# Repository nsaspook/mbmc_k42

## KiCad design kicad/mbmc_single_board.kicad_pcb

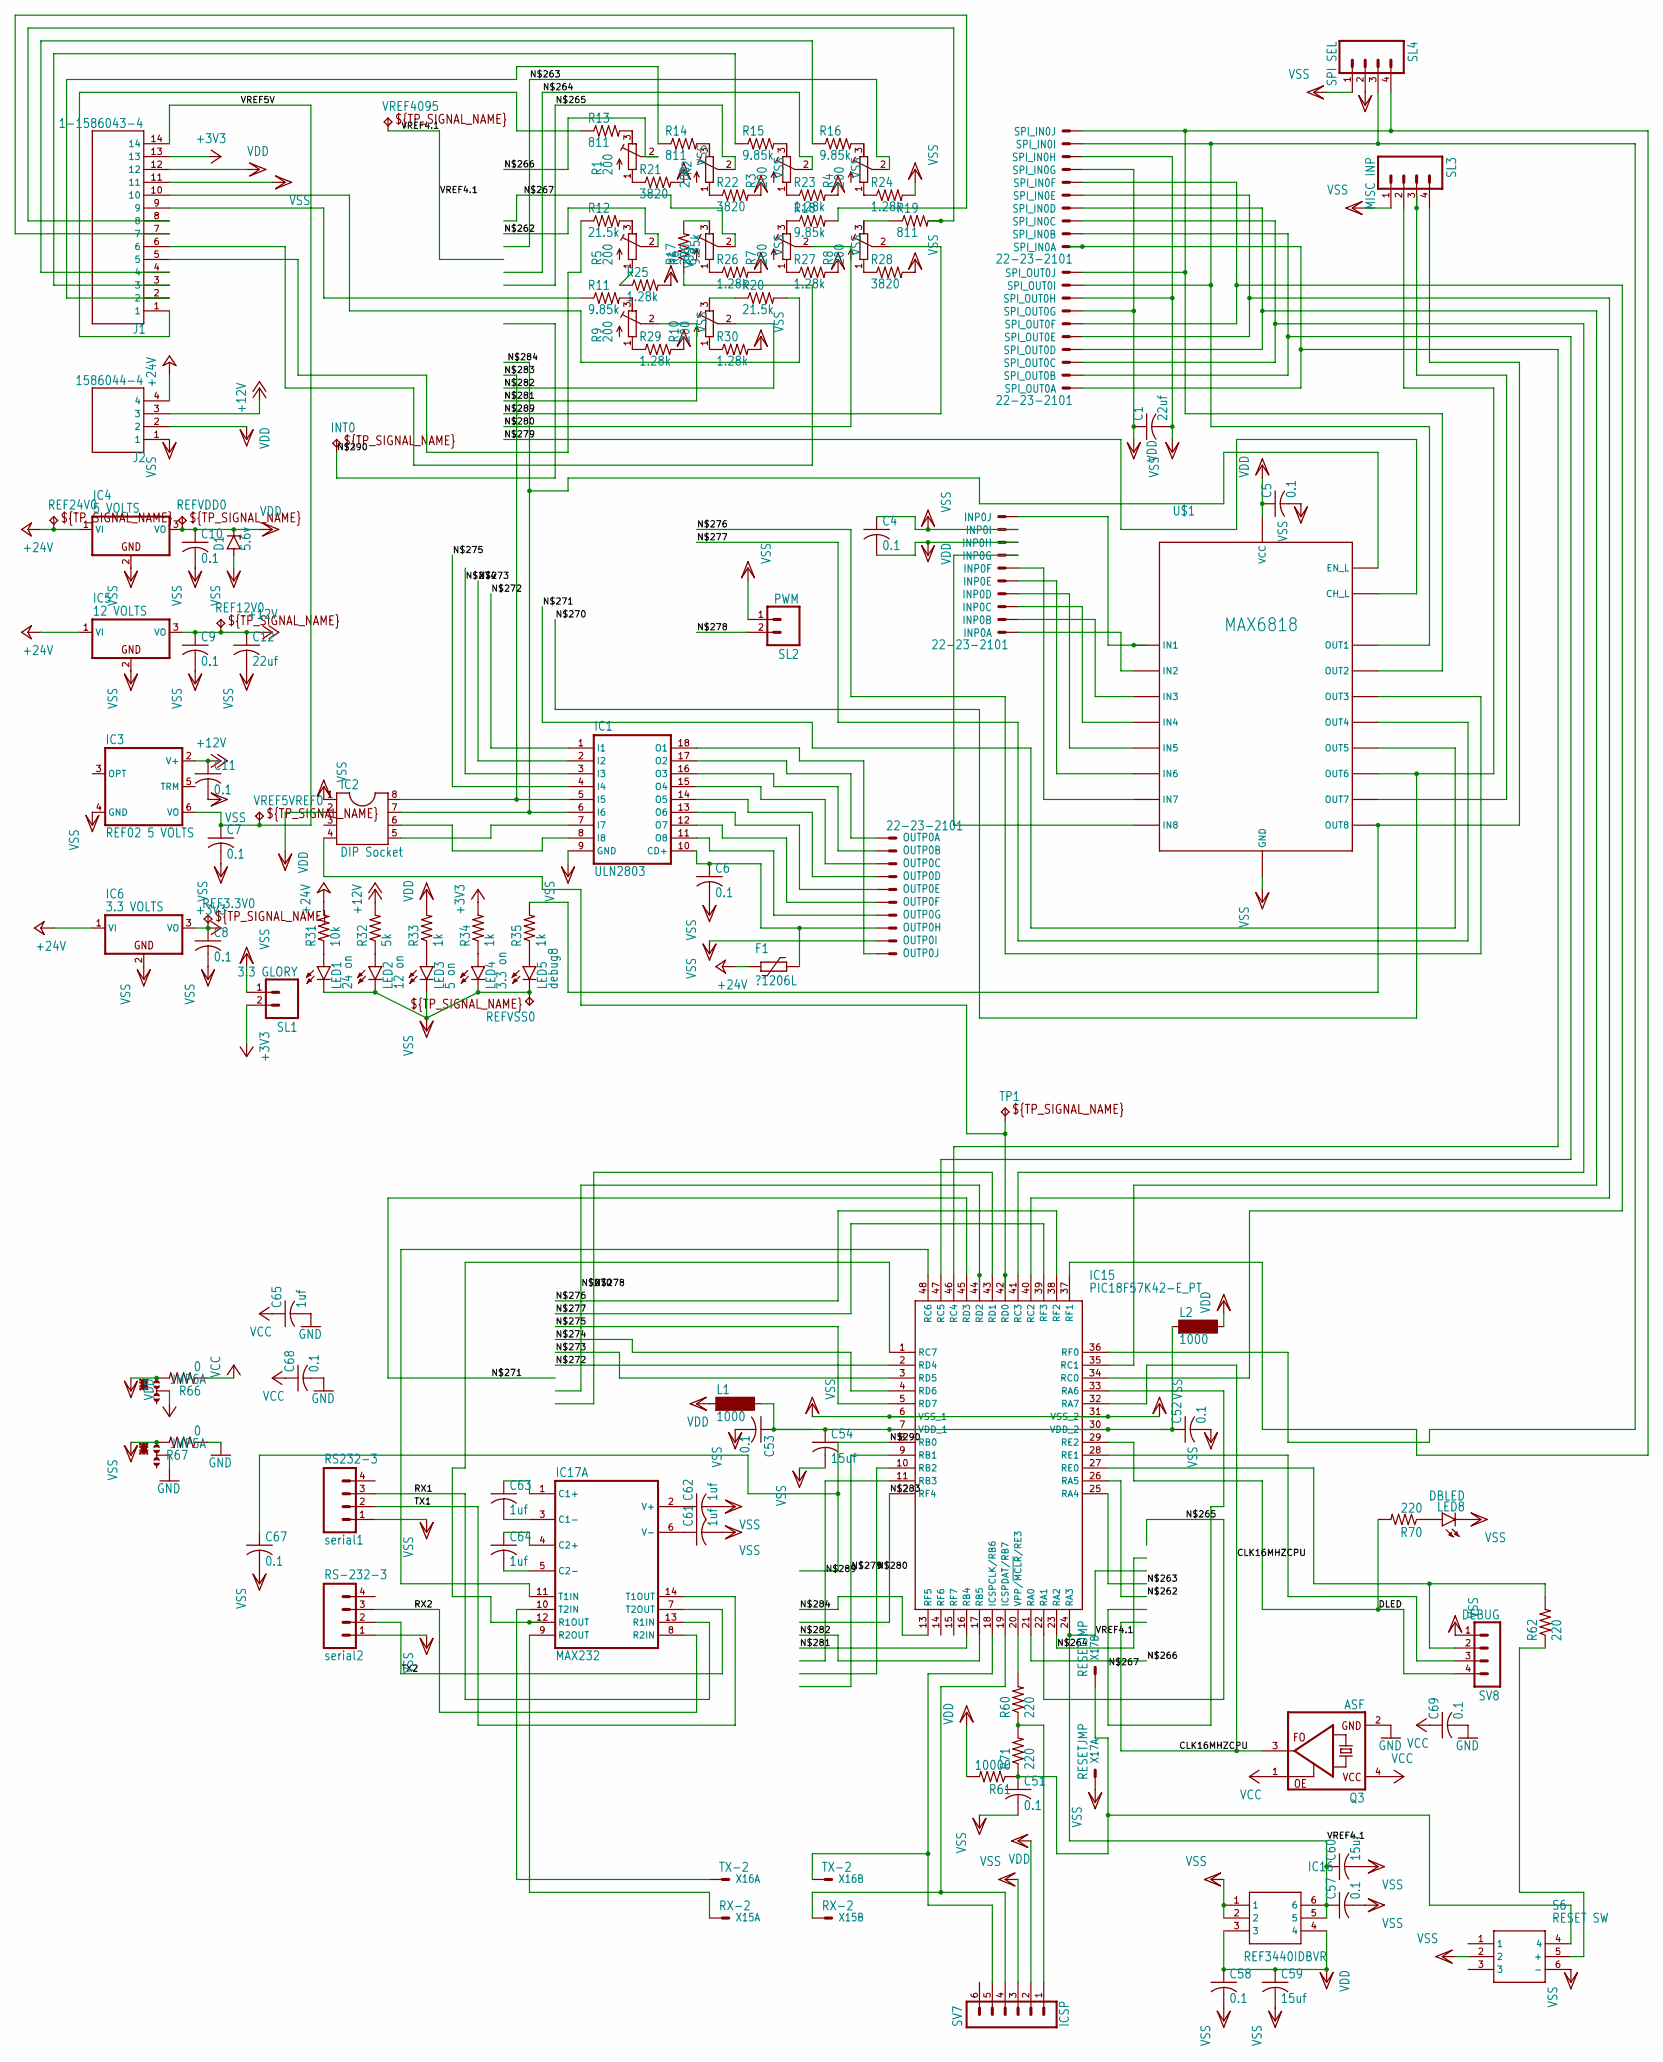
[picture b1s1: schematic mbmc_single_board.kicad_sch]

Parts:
C1, C12: 22uf; C0805
C4, C5, C6, C7, C8, C9, C10, C11: 0.1; C0805
C51, C52, C53, C57, C58, C67, C68, C69: 0.1; C1206
C54, C59, C60: 15uf; C1206
C61, C62, C63, C64, C65: 1uf; C0805
D1: 5.6v; ZDIO-2.5
F1: ?1206L; 1206L
IC1: ULN2803; DIL18
IC2: DIP Socket; SOCKET-08
IC3: REF02 5 VOLTS; DIL08
IC4: 5 VOLTS; TO220V
IC5: 12 VOLTS; TO220V
IC6: 3.3 VOLTS; TO220V
IC15: PIC18F57K42-E_PT; QFP50P900X900X120-48N
IC16: REF3440IDBVR; SOP95P280X145-6N
IC17: MAX232; DIL16
INP0: 22-23-2101
INT0: TPB1,27; B1,27
J1: 1-1586043-4; TE_1-1586043-4
J2: 1586044-4; TE_1586044-4
JMP5, JMP6: 0R-JUMPA; A0R-JMP
L1, L2: 1000; SM-1206
LED1: 24 on; CHIPLED_1206
LED2: 12 on; CHIPLED_1206
LED3: 5 on; CHIPLED_1206
LED4: 3.3 on; CHIPLED_1206
LED5: debug8; CHIPLED_1206
LED8: DBLED; CHIPLED_1206
OUTP0: 22-23-2101
Q3: ASF
R1, R2, R3, R4, R5, R6, R7, R8, R9, R10: 200; RTRIM3339P
R11, R15, R16, R17, R18: 9.85k; R0805
R12, R20: 21.5k; R0805
R13, R14, R19: 811; R0805
R21, R22, R28: 3820; R0805
R23, R24, R25, R26, R27, R29, R30: 1.28k; R0805
R31: 10k; R0805
R32: 5k; R0805
R33, R34, R35: 1k; R0805
R60, R62, R70, R71: 220; R1206
R61: 10000; R1206
R66, R67: 0; R1206
REF3.3V0, REF12V0, REF24V0: TPB1,27; B1,27
REFVDD0: TPB1,27; B1,27
REFVSS0: TPB1,27; B1,27
RS232-3: serial1; 04P
RS-232-3: serial2; 04P
S6: RESET SW; B3W-9_1-LED
SL1: 3.3 GLORY; 02P
SL2: PWM; 02P
SL3: MISC INP; 04P
SL4: SPI SEL; 04P
SPI_IN0: 22-23-2101
SPI_OUT0: 22-23-2101
SV7: ICSP; MA06-1
SV8: DEBUG; MA04-1
TP1: TPB1,27; B1,27
U$1: MAX6818; SSOP20
VREF5VREF0, VREF4095: TPB1,27; B1,27
X15: RX-2; 332-02
X16: TX-2; 332-02
X17: RESETJMP; 332-02

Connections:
+3V3: C8.1, IC6.3 (VO), J1.13, R34.2, REF3.3V0.TP, SL1.2
+12V: C9.1, C11.1, C12.1, IC3.2 (V+), IC5.3 (VO), J2.3, R32.2, REF12V0.TP
+24V: F1.2, IC4.1 (VI), IC5.1 (VI), IC6.1 (VI), J2.4, R31.2, REF24V0.TP
CLK16MHZCPU: IC15.32 (RA7), Q3.3 (FO)
DLED: IC15.29 (RE2), R70.2, SV8.4
GND: C65.2, C68.2, C69.2, IC17.15 (GND), JMP5.2, Q3.2 (GND), R67.1
unnamed: R9.3 (E), R11.2
unnamed: R5.3 (E), R12.2
unnamed: R1.3 (E), R13.2
unnamed: R2.3 (E), R14.2
unnamed: R3.3 (E), R15.2
unnamed: R4.3 (E), R16.2
unnamed: R6.3 (E), R17.2
unnamed: J1.7, R18.2
unnamed: R8.3 (E), R19.1
unnamed: J1.8, R19.2
unnamed: R1.1 (A), R21.1
unnamed: R2.1 (A), R22.1
unnamed: R3.1 (A), R23.1
unnamed: R4.1 (A), R24.1
unnamed: R5.1 (A), R25.1
unnamed: R6.1 (A), R26.1
unnamed: R7.1 (A), R27.1
unnamed: R8.1 (A), R28.1
unnamed: R9.1 (A), R29.1
unnamed: R10.1 (A), R30.1
unnamed: C6.1, F1.1, IC1.10 (CD+), OUTP0.8
unnamed: C52.1, C53.1, C54.1, IC15.7 (VDD_1), IC15.30 (VDD_2), L1.2, L2.1
unnamed: J1.2, R14.1
unnamed: IC1.7 (I7), IC2.5
unnamed: IC1.8 (I8), IC2.6
unnamed: IC15.36 (RF0), SL4.3, SPI_IN0.9, SPI_OUT0.9, U$1.OUT1
unnamed: INP0.10, U$1.IN1
unnamed: INP0.1, U$1.IN2
unnamed: INP0.2, U$1.IN3
unnamed: INP0.3, U$1.IN4
unnamed: INP0.4, U$1.IN5
unnamed: INP0.5, U$1.IN6
unnamed: INP0.6, U$1.IN7
unnamed: INP0.7, U$1.IN8
unnamed: IC1.18 (O1), OUTP0.10
unnamed: IC1.17 (O2), OUTP0.1
unnamed: IC1.16 (O3), OUTP0.2
unnamed: IC1.15 (O4), OUTP0.3
unnamed: IC1.14 (O5), OUTP0.4
unnamed: IC1.13 (O6), OUTP0.5
unnamed: IC1.12 (O7), OUTP0.6
unnamed: IC1.11 (O8), OUTP0.7
unnamed: IC15.46 (RC4), SPI_IN0.1, SPI_OUT0.1
unnamed: J1.4, R16.1
unnamed: J1.9, R11.1
unnamed: J1.3, R15.1
unnamed: J1.10, R20.2
unnamed: J1.5, R12.1
unnamed: J1.6, R17.1
unnamed: J1.1, R13.1
unnamed: LED1.A, R31.1
unnamed: LED2.A, R32.1
unnamed: LED3.A, R33.1
unnamed: LED4.A, R34.1
unnamed: LED5.A, R35.1
unnamed: R35.2, SL3.4, U$1.OUT8
unnamed: R10.3 (E), R20.1
unnamed: SL3.3, U$1.OUT7
unnamed: R7.3 (E), R18.1
unnamed: IC15.20 (VPP/~MCLR/RE3), R60.2
unnamed: IC15.19 (ICSPDAT/RB7), SV7.4, X15.2
unnamed: IC15.18 (ICSPCLK/RB6), SV7.5, X16.2
unnamed: C61.1, IC17.6 (V-)
unnamed: C62.1, IC17.2 (V+)
unnamed: C63.1, IC17.1 (C1+)
unnamed: C64.1, IC17.4 (C2+)
unnamed: C64.2, IC17.5 (C2-)
unnamed: C63.2, IC17.3 (C1-)
unnamed: IC15.1 (RC7), IC17.12 (R1OUT)
unnamed: IC17.9 (R2OUT), X15.1
unnamed: IC15.48 (RC6), IC17.11 (T1IN)
unnamed: IC17.10 (T2IN), X16.1
unnamed: R62.1, S6.5 (+)
unnamed: IC15.27 (RE0), R62.2, SV8.2
unnamed: IC15.28 (RE1), SV8.3
unnamed: IC2.4, IC15.42 (RD0), TP1.TP
unnamed: IC15.47 (RC5), SPI_IN0.2, SPI_OUT0.2
unnamed: IC15.41 (RC3), SPI_IN0.3, SPI_OUT0.3
unnamed: IC15.35 (RC1), SPI_IN0.4, SPI_OUT0.4
unnamed: IC15.40 (RC2), SPI_IN0.5, SPI_OUT0.5
unnamed: IC15.34 (RC0), SPI_IN0.6, SPI_OUT0.6
unnamed: IC15.26 (RA5), R5.2 (S)
unnamed: IC15.25 (RA4), R4.2 (S)
unnamed: IC15.23 (RA2), R3.2 (S)
unnamed: IC15.22 (RA1), R2.2 (S)
unnamed: IC15.21 (RA0), R1.2 (S)
unnamed: IC15.33 (RA6), R6.2 (S)
unnamed: IC15.37 (RF1), SL4.4, SPI_IN0.10, SPI_OUT0.10, U$1.OUT2
unnamed: IC15.44 (RD2), SL3.2, U$1.OUT6
unnamed: IC15.45 (RD3), U$1.OUT5
unnamed: IC1.1 (I1), IC15.2 (RD4)
unnamed: IC1.2 (I2), IC15.3 (RD5)
unnamed: IC1.3 (I3), IC15.4 (RD6)
unnamed: IC1.4 (I4), IC15.5 (RD7)
unnamed: IC15.38 (RF2), U$1.OUT3
unnamed: IC15.39 (RF3), U$1.OUT4
unnamed: IC15.43 (RD1), SL2.2
unnamed: IC15.9 (RB1), U$1.CH_L
unnamed: IC15.10 (RB2), R7.2 (S)
unnamed: IC15.16 (RB4), R9.2 (S)
unnamed: IC15.17 (RB5), R10.2 (S)
unnamed: IC1.5 (I5), IC2.8, IC15.12 (RF4)
unnamed: IC1.6 (I6), IC2.7, IC15.13 (RF5), U$1.EN_L
unnamed: IC15.11 (RB3), R8.2 (S)
unnamed: C67.1, IC15.8 (RB0), INT0.TP
unnamed: LED8.A, R70.1
unnamed: C51.1, R61.1, R71.1, S6.4, X17.2
unnamed: R60.1, R71.2, SV7.1
RX1: IC17.13 (R1IN), RS232-3.3
RX2: IC17.8 (R2IN), RS-232-3.3
TX1: IC17.14 (T1OUT), RS232-3.2
TX2: IC17.7 (T2OUT), RS-232-3.2
VCC: C65.1, C68.1, C69.1, IC17.16 (VCC), JMP6.2, Q3.1 (OE), Q3.4 (VCC), R66.1
VDD: C1.1, C4.2, C5.1, C10.1, C58.1, C59.1, D1.C, IC2.2, IC4.3 (VO), IC16.3, IC16.4, INP0.8, J1.12, J2.2, JMP6.1, L1.1, L2.2, R33.2, R61.2, R66.2, REFVDD0.TP, SL4.2, SPI_IN0.7, SPI_OUT0.7, SV7.2, U$1.VCC
VREF4.1: C57.1, C60.1, IC15.24 (RA3), IC16.5, IC16.6, VREF4095.TP
VREF5V: C7.1, IC3.6 (VO), J1.14, VREF5VREF0.TP
VSS: C1.2, C4.1, C5.2, C6.2, C7.2, C8.2, C9.2, C10.2, C11.2, C12.2, C51.2, C52.2, C53.2, C54.2, C57.2, C58.2, C59.2, C60.2, C61.2, C62.2, C67.2, D1.A, IC1.9 (GND), IC2.1, IC3.4 (GND), IC4.2 (GND), IC5.2 (GND), IC6.2 (GND), IC15.6 (VSS_1), IC15.31 (VSS_2), IC16.1, IC16.2, INP0.9, J1.11, J2.1, JMP5.1, LED1.C, LED2.C, LED3.C, LED4.C, LED5.C, LED8.C, OUTP0.9, R21.2, R22.2, R23.2, R24.2, R25.2, R26.2, R27.2, R28.2, R29.2, R30.2, R67.2, REFVSS0.TP, RS232-3.1, RS-232-3.1, S6.2, S6.6 (-), SL1.1, SL2.1, SL3.1, SL4.1, SPI_IN0.8, SPI_OUT0.8, SV7.3, SV8.1, U$1.GND, X17.1

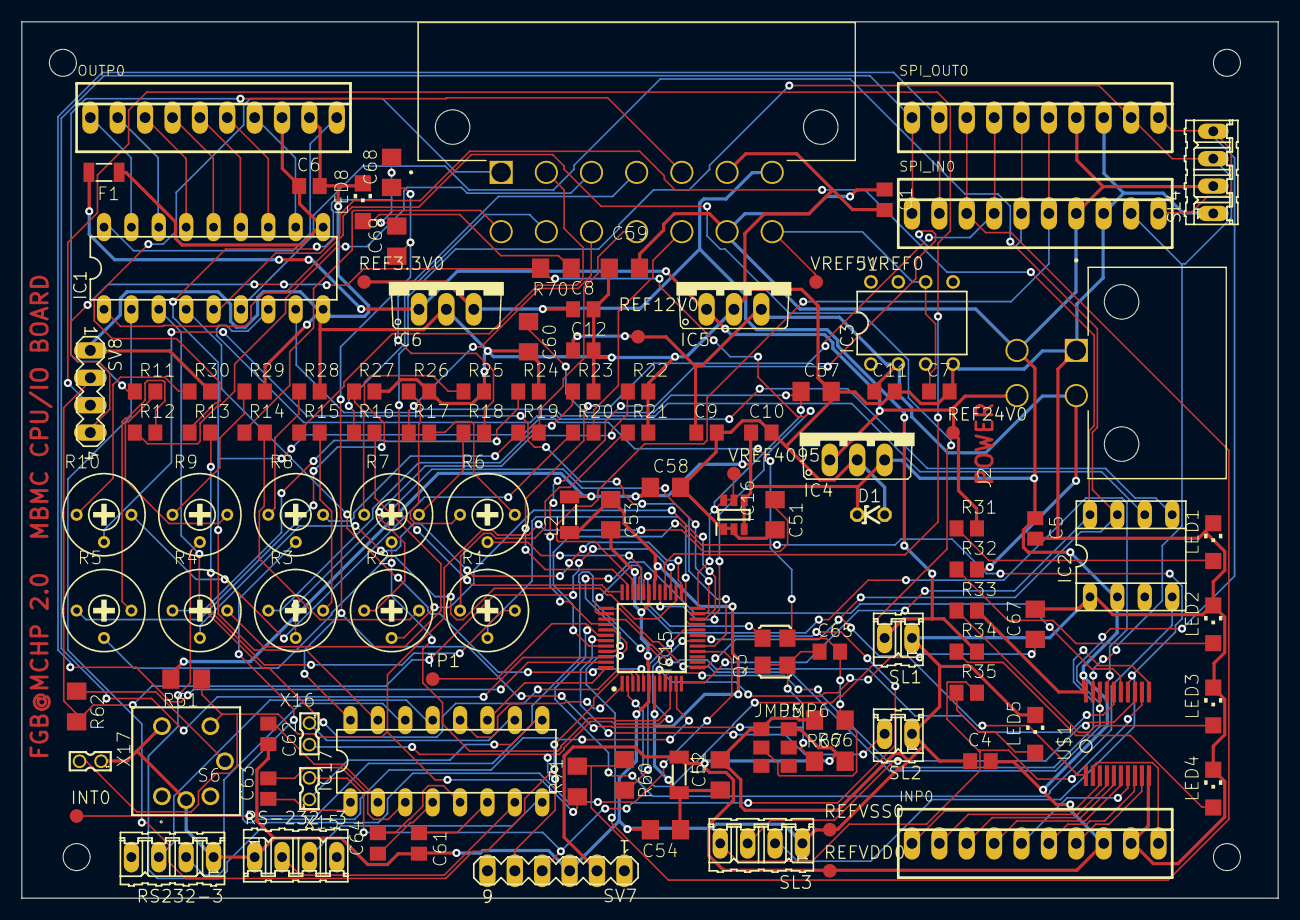
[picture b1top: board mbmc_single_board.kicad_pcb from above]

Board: 2 copper layers, 116.5 x 81.3 mm, 122 parts (0 on the bottom side), 123 nets.

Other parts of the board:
@HOLE0, @HOLE1, @HOLE2, @HOLE3: (no value)

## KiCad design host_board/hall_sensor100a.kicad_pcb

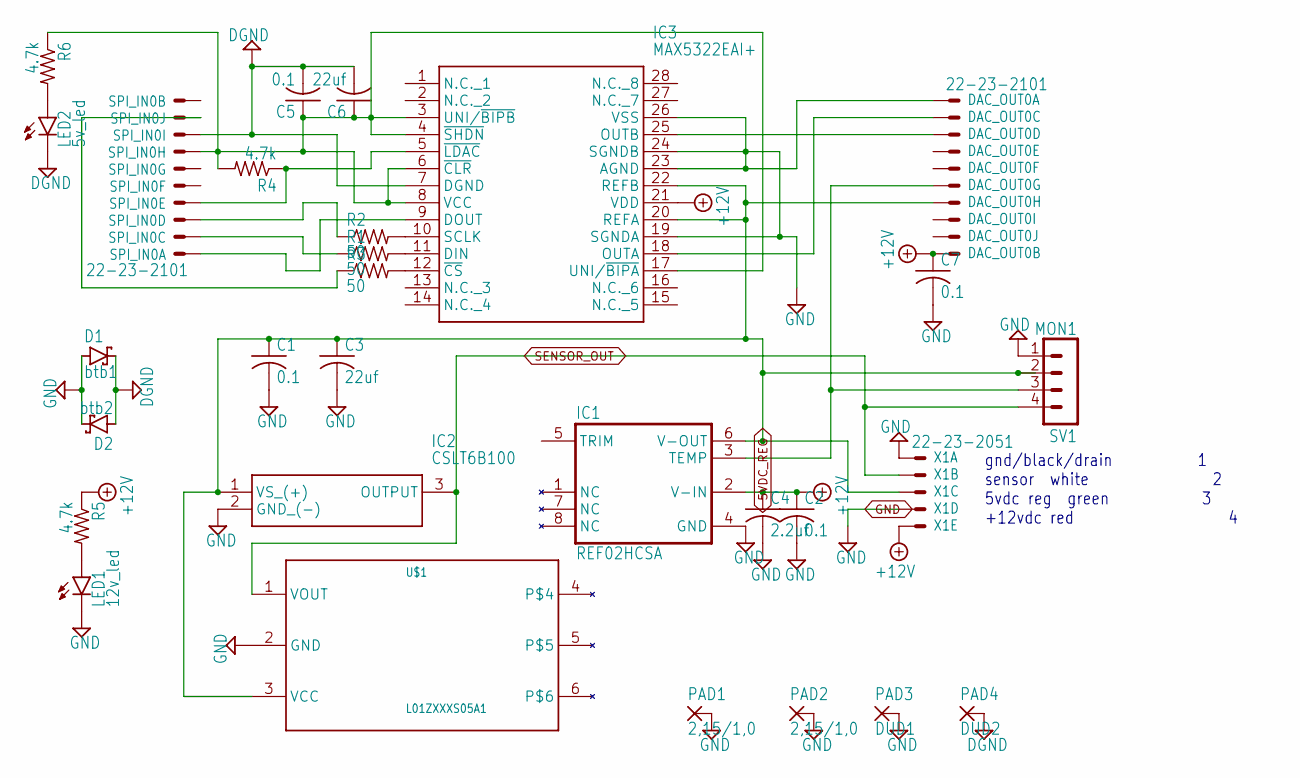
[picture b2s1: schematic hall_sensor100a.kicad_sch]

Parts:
C1, C2, C5, C7: 0.1; C0805
C3, C6: 22uf; C0805
C4: 2.2uf; C0805
D1: btb1; DO35-7
D2: btb2; DO35-7
DAC_OUT0: 22-23-2101; MPN 22-23-2101
IC1: REF02HCSA; SO08
IC2: CSLT6B100; MANUFACTURER_PART_NUMBER CSLT6B100; MOUSER_PART_NUMBER 785-CSLT6B100
IC3: MAX5322EAI+; SOP65P778X199-28N; MANUFACTURER_PART_NUMBER MAX5322EAI+; MOUSER_PART_NUMBER 700-MAX5322EAI
LED1: 12v_led; CHIPLED_1206
LED2: 5v_led; CHIPLED_1206
PAD1, PAD2: 2,15/1,0; 2,15_1,0
PAD3: DUD1; 2,15_1,0
PAD4: DUD2; 2,15_1,0
R1, R2, R3: 50; M0805
R4, R5, R6: 4.7k; M0805
SPI_IN0: 22-23-2101; MPN 22-23-2101
SV1: MON1; MA04-1
U$1: L01ZXXXS05A1; DIP2540W53P254L2900H508Q6B
X1: 22-23-2051; MPN 22-23-2051

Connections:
5VDC_REG: C1.1, C3.1, DAC_OUT0.7, IC1.6 (V-OUT), IC2.1 (VS_(+)), IC3.20 (REFA), IC3.22 (REFB), SV1.2, U$1.3 (VCC), X1.3
+12V: C2.1, C4.1, C7.1, DAC_OUT0.10, IC1.2 (V-IN), IC3.21 (VDD), R5.1, X1.5
DGND: C5.2, C6.2, D1.C, D2.A, IC3.7 (DGND), LED2.C, PAD4.1, SPI_IN0.8
GND: C1.2, C2.2, C3.2, C4.2, C7.2, D1.A, D2.C, DAC_OUT0.1, IC1.4 (GND), IC2.2 (GND_(-)), IC3.19 (SGNDA), IC3.23 (AGND), IC3.24 (SGNDB), IC3.26 (VSS), LED1.C, PAD1.1, PAD2.1, PAD3.1, SV1.1, U$1.2 (GND), X1.1, X1.4
unnamed: IC3.11 (DIN), R1.2
unnamed: DAC_OUT0.2, IC3.18 (OUTA)
unnamed: DAC_OUT0.3, IC3.25 (OUTB)
unnamed: R1.1, SPI_IN0.2
unnamed: IC3.9 (DOUT), SPI_IN0.1
unnamed: R2.1, SPI_IN0.3
unnamed: R3.1, SPI_IN0.9
unnamed: C5.1, C6.1, IC3.3 (UNI/~BIPB), IC3.4 (~SHDN), IC3.6 (~CLR), IC3.8 (VCC), IC3.17 (UNI/~BIPA), R4.2, R6.1, SPI_IN0.7
unnamed: LED1.A, R5.2
unnamed: IC3.5 (~LDAC), R4.1, SPI_IN0.4
unnamed: IC3.10 (SCLK), R2.2
unnamed: IC3.12 (~CS), R3.2
unnamed: DAC_OUT0.6, IC1.3 (TEMP), SV1.3
unnamed: LED2.A, R6.2
SENSOR_OUT: IC2.3 (OUTPUT), SV1.4, U$1.1 (VOUT), X1.2

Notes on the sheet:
gnd/black/drain 1 sensor white 2 5vdc reg green 3 +12vdc red 4

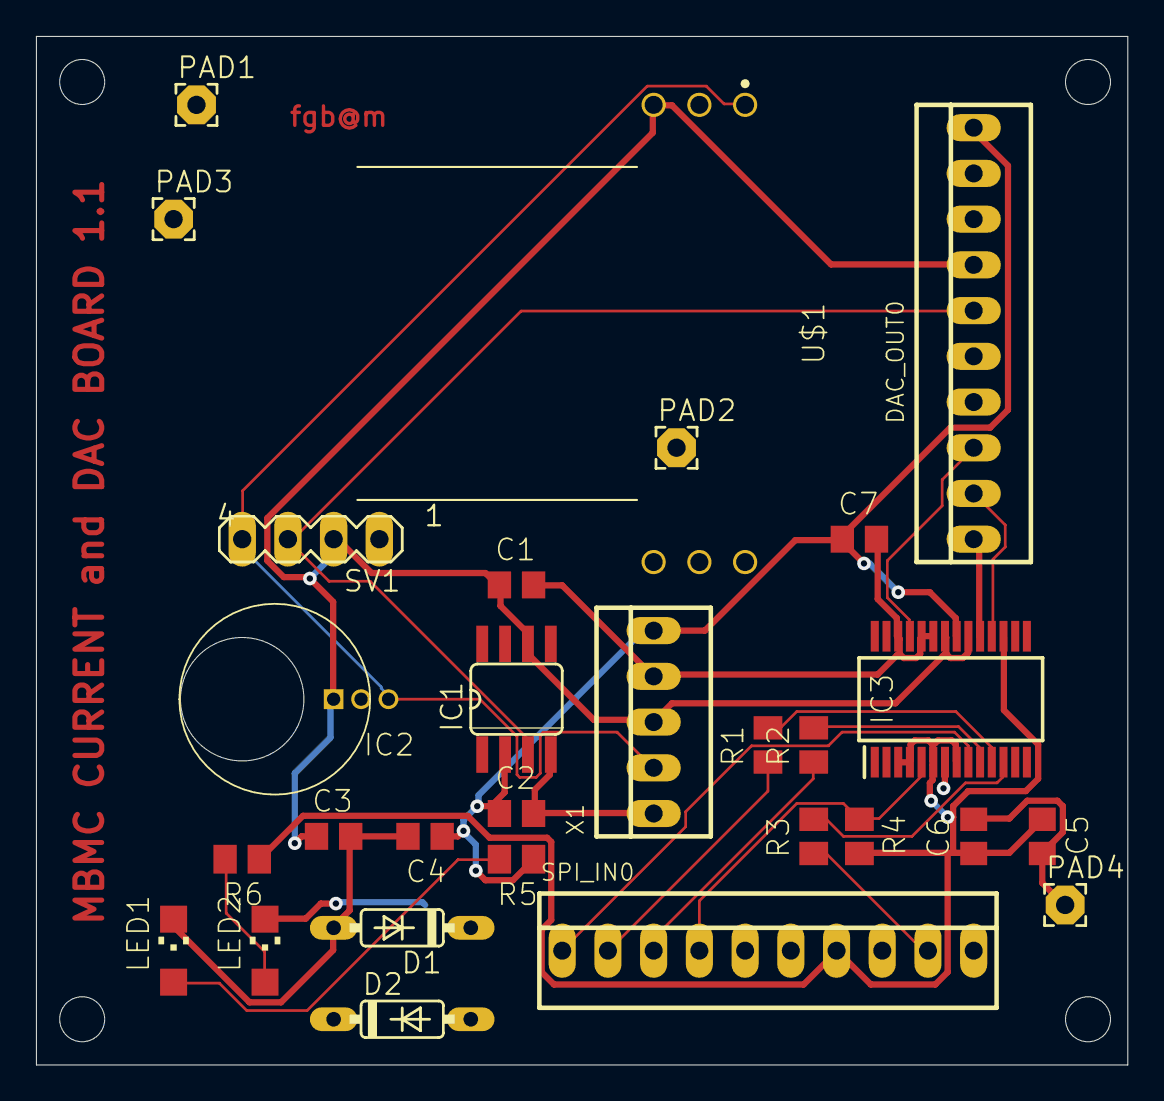
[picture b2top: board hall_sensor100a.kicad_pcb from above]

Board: 2 copper layers, 60.6 x 57.1 mm, 34 parts (0 on the bottom side), 19 nets.

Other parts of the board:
UNK_HOLE_0: dummyfp0
UNK_HOLE_1: dummyfp1
UNK_HOLE_2: dummyfp2
UNK_HOLE_3: dummyfp3
UNK_HOLE_4: dummyfp4

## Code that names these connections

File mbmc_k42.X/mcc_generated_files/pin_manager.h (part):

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// get/set C_BATT aliases
#define C_BATT_TRIS                 TRISAbits.TRISA0
#define C_BATT_LAT                  LATAbits.LATA0
#define C_BATT_PORT                 PORTAbits.RA0
#define C_BATT_WPU                  WPUAbits.WPUA0
#define C_BATT_OD                   ODCONAbits.ODCA0
#define C_BATT_ANS                  ANSELAbits.ANSELA0
#define C_BATT_SetHigh()            do { LATAbits.LATA0 = 1; } while(0)
#define C_BATT_SetLow()             do { LATAbits.LATA0 = 0; } while(0)
#define C_BATT_Toggle()             do { LATAbits.LATA0 = ~LATAbits.LATA0; } while(0)
#define C_BATT_GetValue()           PORTAbits.RA0
#define C_BATT_SetDigitalInput()    do { TRISAbits.TRISA0 = 1; } while(0)
#define C_BATT_SetDigitalOutput()   do { TRISAbits.TRISA0 = 0; } while(0)
#define C_BATT_SetPullup()          do { WPUAbits.WPUA0 = 1; } while(0)
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// get/set C_PV aliases
#define C_PV_TRIS                 TRISAbits.TRISA1
#define C_PV_LAT                  LATAbits.LATA1
#define C_PV_PORT                 PORTAbits.RA1
#define C_PV_WPU                  WPUAbits.WPUA1
#define C_PV_OD                   ODCONAbits.ODCA1
#define C_PV_ANS                  ANSELAbits.ANSELA1
#define C_PV_SetHigh()            do { LATAbits.LATA1 = 1; } while(0)
#define C_PV_SetLow()             do { LATAbits.LATA1 = 0; } while(0)
#define C_PV_Toggle()             do { LATAbits.LATA1 = ~LATAbits.LATA1; } while(0)
#define C_PV_GetValue()           PORTAbits.RA1
#define C_PV_SetDigitalInput()    do { TRISAbits.TRISA1 = 1; } while(0)
#define C_PV_SetDigitalOutput()   do { TRISAbits.TRISA1 = 0; } while(0)
#define C_PV_SetPullup()          do { WPUAbits.WPUA1 = 1; } while(0)
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// get/set V_CC aliases
#define V_CC_TRIS                 TRISAbits.TRISA2
#define V_CC_LAT                  LATAbits.LATA2
#define V_CC_PORT                 PORTAbits.RA2
#define V_CC_WPU                  WPUAbits.WPUA2
#define V_CC_OD                   ODCONAbits.ODCA2
#define V_CC_ANS                  ANSELAbits.ANSELA2
#define V_CC_SetHigh()            do { LATAbits.LATA2 = 1; } while(0)
#define V_CC_SetLow()             do { LATAbits.LATA2 = 0; } while(0)
#define V_CC_Toggle()             do { LATAbits.LATA2 = ~LATAbits.LATA2; } while(0)
#define V_CC_GetValue()           PORTAbits.RA2
#define V_CC_SetDigitalInput()    do { TRISAbits.TRISA2 = 1; } while(0)
#define V_CC_SetDigitalOutput()   do { TRISAbits.TRISA2 = 0; } while(0)
#define V_CC_SetPullup()          do { WPUAbits.WPUA2 = 1; } while(0)
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#define RA3_SetHigh()            do { LATAbits.LATA3 = 1; } while(0)
#define RA3_SetLow()             do { LATAbits.LATA3 = 0; } while(0)
#define RA3_Toggle()             do { LATAbits.LATA3 = ~LATAbits.LATA3; } while(0)
#define RA3_GetValue()              PORTAbits.RA3
#define RA3_SetDigitalInput()    do { TRISAbits.TRISA3 = 1; } while(0)
#define RA3_SetDigitalOutput()   do { TRISAbits.TRISA3 = 0; } while(0)
#define RA3_SetPullup()             do { WPUAbits.WPUA3 = 1; } while(0)
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// get/set V_BAT aliases
#define V_BAT_TRIS                 TRISAbits.TRISA4
#define V_BAT_LAT                  LATAbits.LATA4
#define V_BAT_PORT                 PORTAbits.RA4
#define V_BAT_WPU                  WPUAbits.WPUA4
#define V_BAT_OD                   ODCONAbits.ODCA4
#define V_BAT_ANS                  ANSELAbits.ANSELA4
#define V_BAT_SetHigh()            do { LATAbits.LATA4 = 1; } while(0)
#define V_BAT_SetLow()             do { LATAbits.LATA4 = 0; } while(0)
#define V_BAT_Toggle()             do { LATAbits.LATA4 = ~LATAbits.LATA4; } while(0)
#define V_BAT_GetValue()           PORTAbits.RA4
#define V_BAT_SetDigitalInput()    do { TRISAbits.TRISA4 = 1; } while(0)
#define V_BAT_SetDigitalOutput()   do { TRISAbits.TRISA4 = 0; } while(0)
#define V_BAT_SetPullup()          do { WPUAbits.WPUA4 = 1; } while(0)
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// get/set V_PV aliases
#define V_PV_TRIS                 TRISAbits.TRISA5
#define V_PV_LAT                  LATAbits.LATA5
#define V_PV_PORT                 PORTAbits.RA5
#define V_PV_WPU                  WPUAbits.WPUA5
#define V_PV_OD                   ODCONAbits.ODCA5
#define V_PV_ANS                  ANSELAbits.ANSELA5
#define V_PV_SetHigh()            do { LATAbits.LATA5 = 1; } while(0)
#define V_PV_SetLow()             do { LATAbits.LATA5 = 0; } while(0)
#define V_PV_Toggle()             do { LATAbits.LATA5 = ~LATAbits.LATA5; } while(0)
#define V_PV_GetValue()           PORTAbits.RA5
#define V_PV_SetDigitalInput()    do { TRISAbits.TRISA5 = 1; } while(0)
#define V_PV_SetDigitalOutput()   do { TRISAbits.TRISA5 = 0; } while(0)
#define V_PV_SetPullup()          do { WPUAbits.WPUA5 = 1; } while(0)
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// get/set V_CMODE aliases
#define V_CMODE_TRIS                 TRISAbits.TRISA6
#define V_CMODE_LAT                  LATAbits.LATA6
#define V_CMODE_PORT                 PORTAbits.RA6
#define V_CMODE_WPU                  WPUAbits.WPUA6
#define V_CMODE_OD                   ODCONAbits.ODCA6
#define V_CMODE_ANS                  ANSELAbits.ANSELA6
#define V_CMODE_SetHigh()            do { LATAbits.LATA6 = 1; } while(0)
#define V_CMODE_SetLow()             do { LATAbits.LATA6 = 0; } while(0)
#define V_CMODE_Toggle()             do { LATAbits.LATA6 = ~LATAbits.LATA6; } while(0)
#define V_CMODE_GetValue()           PORTAbits.RA6
#define V_CMODE_SetDigitalInput()    do { TRISAbits.TRISA6 = 1; } while(0)
#define V_CMODE_SetDigitalOutput()   do { TRISAbits.TRISA6 = 0; } while(0)
#define V_CMODE_SetPullup()          do { WPUAbits.WPUA6 = 1; } while(0)
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#define RB0_SetHigh()            do { LATBbits.LATB0 = 1; } while(0)
#define RB0_SetLow()             do { LATBbits.LATB0 = 0; } while(0)
#define RB0_Toggle()             do { LATBbits.LATB0 = ~LATBbits.LATB0; } while(0)
#define RB0_GetValue()              PORTBbits.RB0
#define RB0_SetDigitalInput()    do { TRISBbits.TRISB0 = 1; } while(0)
#define RB0_SetDigitalOutput()   do { TRISBbits.TRISB0 = 0; } while(0)
#define RB0_SetPullup()             do { WPUBbits.WPUB0 = 1; } while(0)
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#define RB1_SetHigh()            do { LATBbits.LATB1 = 1; } while(0)
#define RB1_SetLow()             do { LATBbits.LATB1 = 0; } while(0)
#define RB1_Toggle()             do { LATBbits.LATB1 = ~LATBbits.LATB1; } while(0)
#define RB1_GetValue()              PORTBbits.RB1
#define RB1_SetDigitalInput()    do { TRISBbits.TRISB1 = 1; } while(0)
#define RB1_SetDigitalOutput()   do { TRISBbits.TRISB1 = 0; } while(0)
#define RB1_SetPullup()             do { WPUBbits.WPUB1 = 1; } while(0)
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// get/set V_BBAT aliases
#define V_BBAT_TRIS                 TRISBbits.TRISB2
#define V_BBAT_LAT                  LATBbits.LATB2
#define V_BBAT_PORT                 PORTBbits.RB2
#define V_BBAT_WPU                  WPUBbits.WPUB2
#define V_BBAT_OD                   ODCONBbits.ODCB2
#define V_BBAT_ANS                  ANSELBbits.ANSELB2
#define V_BBAT_SetHigh()            do { LATBbits.LATB2 = 1; } while(0)
#define V_BBAT_SetLow()             do { LATBbits.LATB2 = 0; } while(0)
#define V_BBAT_Toggle()             do { LATBbits.LATB2 = ~LATBbits.LATB2; } while(0)
#define V_BBAT_GetValue()           PORTBbits.RB2
#define V_BBAT_SetDigitalInput()    do { TRISBbits.TRISB2 = 1; } while(0)
#define V_BBAT_SetDigitalOutput()   do { TRISBbits.TRISB2 = 0; } while(0)
#define V_BBAT_SetPullup()          do { WPUBbits.WPUB2 = 1; } while(0)
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// get/set C_MPPT aliases
#define C_MPPT_TRIS                 TRISBbits.TRISB3
#define C_MPPT_LAT                  LATBbits.LATB3
#define C_MPPT_PORT                 PORTBbits.RB3
#define C_MPPT_WPU                  WPUBbits.WPUB3
#define C_MPPT_OD                   ODCONBbits.ODCB3
#define C_MPPT_ANS                  ANSELBbits.ANSELB3
#define C_MPPT_SetHigh()            do { LATBbits.LATB3 = 1; } while(0)
#define C_MPPT_SetLow()             do { LATBbits.LATB3 = 0; } while(0)
#define C_MPPT_Toggle()             do { LATBbits.LATB3 = ~LATBbits.LATB3; } while(0)
#define C_MPPT_GetValue()           PORTBbits.RB3
#define C_MPPT_SetDigitalInput()    do { TRISBbits.TRISB3 = 1; } while(0)
#define C_MPPT_SetDigitalOutput()   do { TRISBbits.TRISB3 = 0; } while(0)
#define C_MPPT_SetPullup()          do { WPUBbits.WPUB3 = 1; } while(0)
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// get/set V_INVERTER aliases
#define V_INVERTER_TRIS                 TRISBbits.TRISB4
#define V_INVERTER_LAT                  LATBbits.LATB4
#define V_INVERTER_PORT                 PORTBbits.RB4
#define V_INVERTER_WPU                  WPUBbits.WPUB4
#define V_INVERTER_OD                   ODCONBbits.ODCB4
#define V_INVERTER_ANS                  ANSELBbits.ANSELB4
#define V_INVERTER_SetHigh()            do { LATBbits.LATB4 = 1; } while(0)
#define V_INVERTER_SetLow()             do { LATBbits.LATB4 = 0; } while(0)
#define V_INVERTER_Toggle()             do { LATBbits.LATB4 = ~LATBbits.LATB4; } while(0)
#define V_INVERTER_GetValue()           PORTBbits.RB4
#define V_INVERTER_SetDigitalInput()    do { TRISBbits.TRISB4 = 1; } while(0)
#define V_INVERTER_SetDigitalOutput()   do { TRISBbits.TRISB4 = 0; } while(0)
#define V_INVERTER_SetPullup()          do { WPUBbits.WPUB4 = 1; } while(0)
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// get/set V_LIGHT_SENSOR aliases
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
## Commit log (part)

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2020-11-29 new git for MBMC for 24 volt systems
2024-01-30 alpha version 2.10
2024-10-19 correct AH calcs
2025-03-19 clean up files for doxygen docs
2025-08-19 checkpoint

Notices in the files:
mbmc_k42.X/mcc_generated_files/pin_manager.h:
(c) 2018 Microchip Technology Inc. and its subsidiaries.
